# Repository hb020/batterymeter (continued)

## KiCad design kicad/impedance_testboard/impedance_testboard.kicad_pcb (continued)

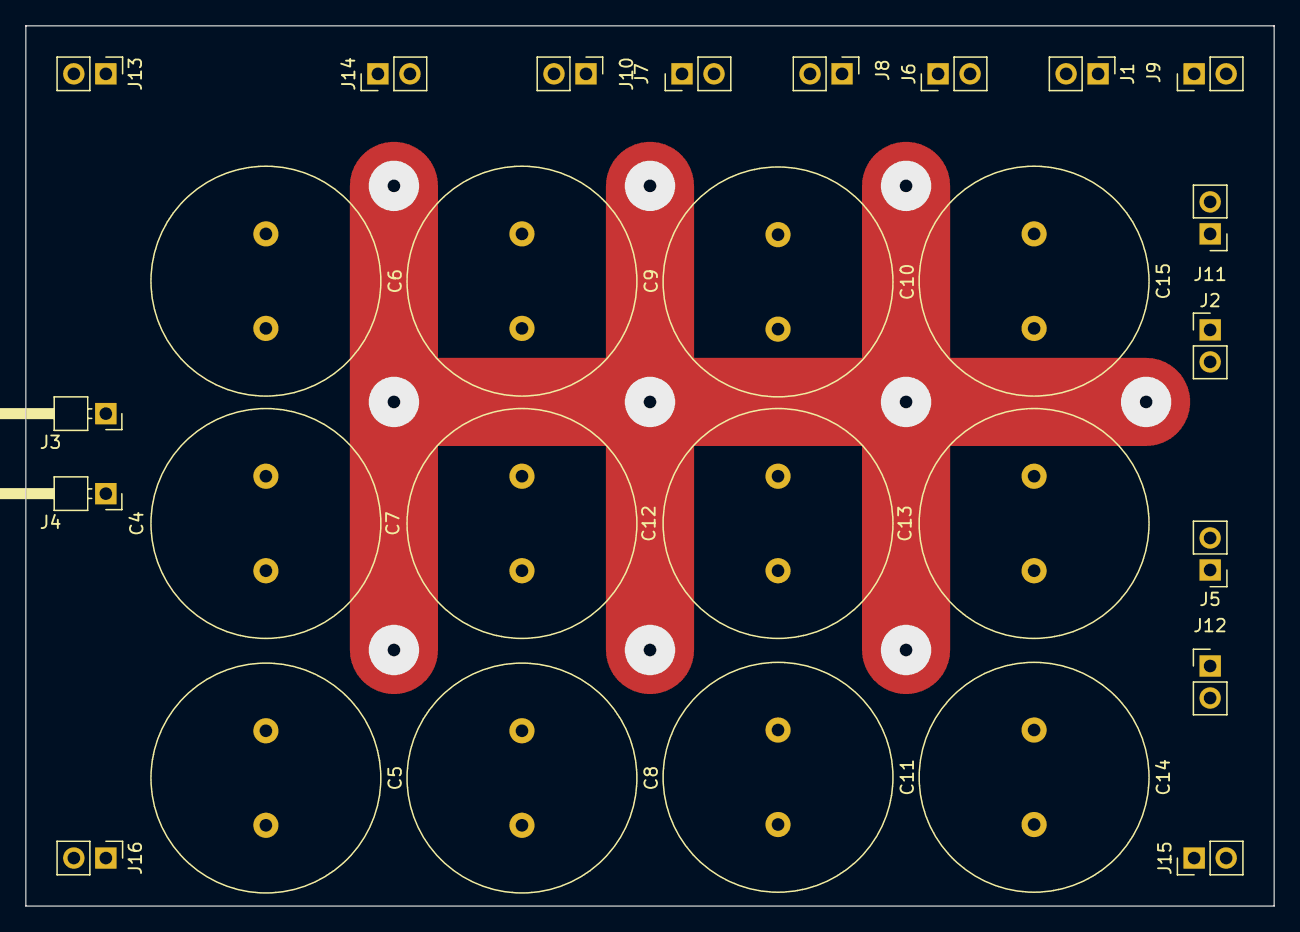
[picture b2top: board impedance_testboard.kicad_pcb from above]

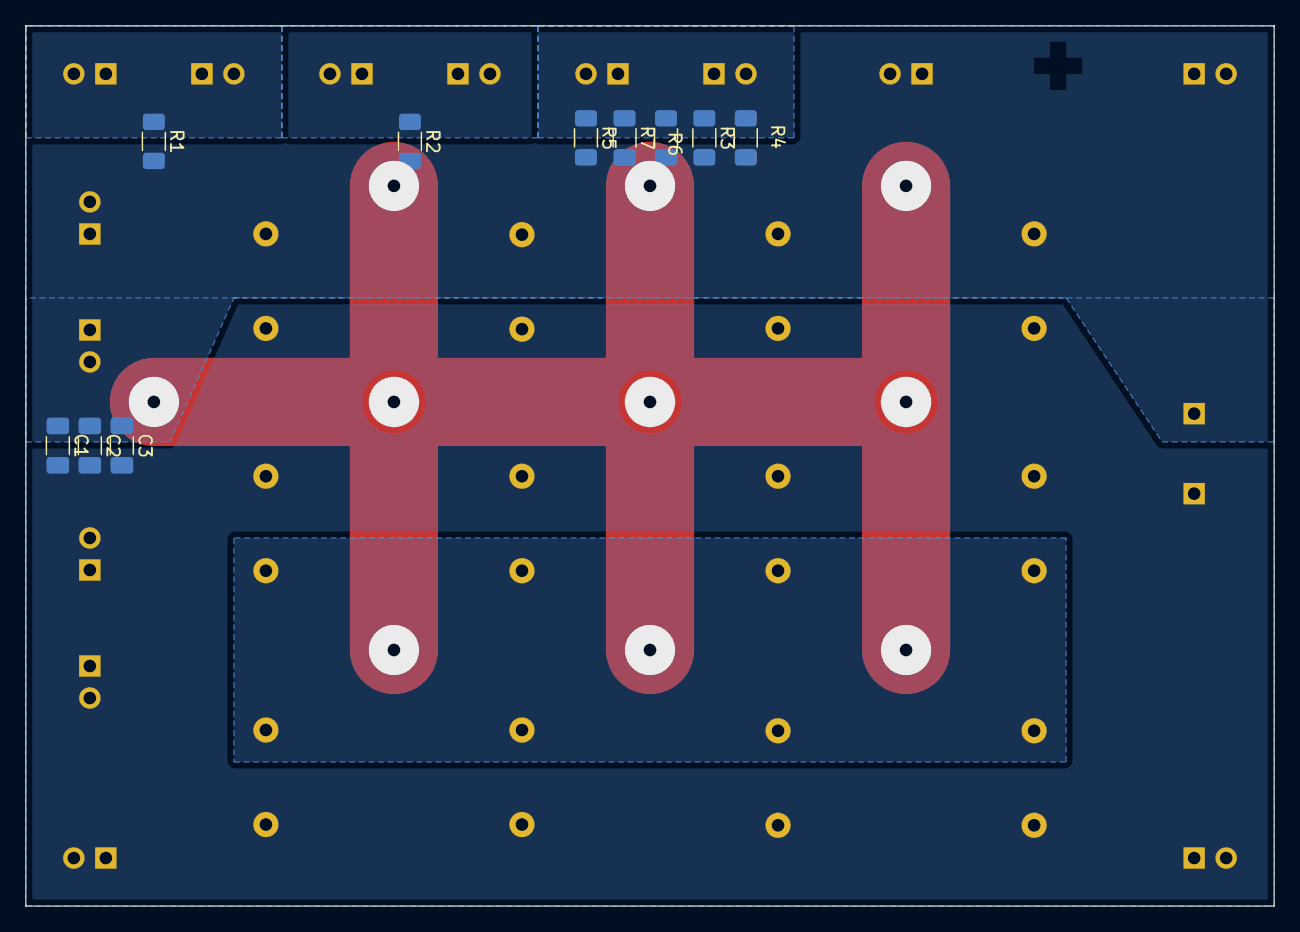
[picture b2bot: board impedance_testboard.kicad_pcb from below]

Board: 2 copper layers, 99.1 x 69.8 mm, 38 parts (10 on the bottom side), 5 nets.

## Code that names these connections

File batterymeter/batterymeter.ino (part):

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//        func               | alt                         | debug use
//--------------------------+-----------------------------+----------------------
// 1  VDD                    |                             |
// 2  PA4 SIGNAL_OUT         | AIN4  !SS     WO4           |
// 3  PA5 free               | PA5 AIN5  VREFA   WO5 0.WO  | PA5 debug AC sampler
// 4  PA6 OUT_SW             | PA6 AIN6                    |
// 5  PA7 CPU_PWR_ON         | PA7 AIN7                    |
// 6  PB5 SHORT_SW           | PB5 AIN8          WO2'      |
// 7  PB4 ADC_IN_SW          | PB4 AIN9  !RESET' WO1'      |
// 8  RxD                    | PB3               WO0'      |
// 9  TxD                    | PB2               WO2       |
// 10 SDA                    | PB1 AIN10         WO1       |
// 11 SCL                    | PB0 AIN11         WO0       |
// 12 PC0 REF_SW_A           | PC0 AIN10 SCK'              |
// 13 PC1 REF_SW_B           | PC1 AIN13 MISO'             |
// 14 PC2 free               | PC2 AIN14 MOSI'             | EVOUTC debug AC sampler
// 15 PC3 SHORT_DISABLE      | PC3 AIN15 !SS'              |
// 16 UPDI                   | PA0 !RESET                  |
// 17 AIN1 ADC_INP           | PA1 MOSI                    |
// 18 AIN2 ADC_INN           | PA2 MISO                    |
// 19 AIN3 ADC_DC            | PA3 AIN3  SCK WO3  1.WO     |
// 20 GND                    |

// AIN[15:8] can not be used as negative ADC input for differential measurements.
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// 100mA  1     1    x      x       1
//

#define SIGNAL_OUT PIN_PA4
//#define AC_SIGNAL_DEBUG_TRIGGERPIN_ON_PC2
//#define AC_SIGNAL_DEBUG_WAITPIN_ON_PA5

#define OUT_SW PIN_PA6
#define CPU_PWR_ON PIN_PA7
#define SHORT_SW PIN_PB5
#define ADC_IN_SW PIN_PB4

#define REF_SW_A PIN_PC0
#define REF_SW_B PIN_PC1

#ifdef BODGE_REF_SW
#ifdef AC_SIGNAL_DEBUG_TRIGGERPIN_ON_PC2
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#endif
#endif

#define SHORT_DISABLE PIN_PC3

#define ADC_INP PIN_PA1
#define ADC_INN PIN_PA2
#define ADC_DC PIN_PA3

// what type of display?
#define OLED_128x32
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    digitalWrite(REF_SW_B, range & 2);
    _iCurrentRange = range;
#ifdef BODGE_REF_SW
    //         PA5   PC2
    //  100uA    1     1
    //    1mA    0     1
    //   10mA    1     0
    //  100mA    0     0
    digitalWrite(PIN_PA5, !(range & 1));
    digitalWrite(PIN_PC2, !(range & 2));
#endif
}

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// Early IO pin setup. Not allowed to do serial or screen printing
void setupIOPins(void) {
    // urgent stuff
    pinMode(CPU_PWR_ON, OUTPUT);
    setPowerOn();

    // The rest
    pinMode(SIGNAL_OUT, OUTPUT);
    digitalWriteFast(SIGNAL_OUT, LOW);
    pinMode(OUT_SW, OUTPUT);
    setTestModeDCIS();  // force 0 current

    pinMode(ADC_IN_SW, OUTPUT);
    setADCInMode(adcin_batt);

    pinMode(REF_SW_A, OUTPUT);
    pinMode(REF_SW_B, OUTPUT);
#ifdef BODGE_REF_SW
    pinMode(PIN_PA5, OUTPUT);
    pinMode(PIN_PC2, OUTPUT);
#endif
    setIRange(range_min);

    pinMode(SHORT_DISABLE, OUTPUT);
    setShortOff();
    pinMode(SHORT_SW, OUTPUT);
    // no need to set it, as short is off
}

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    takeOverTCA0();  // This replaces disabling and resetting the timer, required previously.
}

// pin can be:  0 or PB4 or PB5. (WO1' or WO2') Cannot use PB0..PB3, as they collide with I2C or serial
// if 0: just starts TCA0, which can then be used by EVSYS with OVF. Note that PWM will be useless then
void startToneGen(int pin, unsigned long freqInHz = 16000, byte dutyCycle = 50) {
    unsigned long tempperiod = (F_CPU / freqInHz);
    unsigned long cmpval = 0;
    byte presc = 0;

    if ((pin != 0) && (pin != PIN_PB4) && (pin != PIN_PB5)) {
        Serial.printf("FATAL ERROR: cannot set ToneGen on pin %d, as it is an illegal pin\n", pin);
        return;
    }
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    // Set Alternative outputs
    // Set output and the correct comparator (and therefore the correct pin number)
    // also set the PWM value
    if (pin == PIN_PB4) {
        PORTMUX.TCAROUTEA = PORTMUX_TCA01_ALT1_gc;
        TCA0.SINGLE.CTRLB |= TCA_SINGLE_CMP1EN_bm;
        TCA0.SINGLE.CMP1 = cmpval;
    }
    if (pin == PIN_PB5) {
        PORTMUX.TCAROUTEA = PORTMUX_TCA02_ALT1_gc;
        TCA0.SINGLE.CTRLB |= TCA_SINGLE_CMP2EN_bm;
        TCA0.SINGLE.CMP2 = cmpval;
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    digitalWrite(SIGNAL_OUT, LOW);

#ifdef AC_SIGNAL_DEBUG_WAITPIN_ON_PA5
    pinMode(PIN_PA5, OUTPUT);
    digitalWrite(PIN_PA5, LOW);
#endif

    // Throw the first away, used for setting the ADC thingies
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
#ifdef AC_SIGNAL_DEBUG_TRIGGERPIN_ON_PC2
    // debug
    Event0.set_user(user::evoutc_pin_pc2);  // this provokes a 100ns pulse on PC2
#endif

    had_ADC_ERR = 0;
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//     const float adc_multiplier = 1.0;
//     char buffer[40];

//     rawv = analogReadEnh(PIN_PA1, ADC_RESOLUTION, 0);
//     v1 = round(((float)adc_max_scale * (float)rawv) / (adc_multiplier * (float)adc_max_val_single));

//     rawv = analogReadDiff(PIN_PA1,PIN_PA2, ADC_RESOLUTION, 0);
//     v2 = round(((float)adc_max_scale * (float)rawv) / (adc_multiplier * (float)adc_max_val_diff));

//     oled.setFont(FONT6X8);
//     oled.setCursor(0, 0);
//     sprintf(buffer,"%05ld mV PA1",v1);
//     oled.print(buffer);
//     oled.setCursor(0, 1);
//     sprintf(buffer,"%05ld mV PA1-PA2",v2); // often non-zero, so calibrate that runtime! and 10k input impedance, not great.
//     oled.print(buffer);
//     //Serial.println(v);
// }
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
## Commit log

2023-01-10 First published version
2023-01-10 better explanation of DCIS
2023-01-10 oops in doc
2023-01-10 image size reduce
2023-01-14 improve V reading
2023-01-15 Better explanation of the Why
2023-01-17 better doc
2023-01-28 very small doc correction
2023-01-28 slightly better doc
2023-01-28 again doc..
2023-02-16 better input voltage readings
2023-05-20 Updated the remark on platformio. Platformio is pretty good now.
2024-01-15 scope images were missing
